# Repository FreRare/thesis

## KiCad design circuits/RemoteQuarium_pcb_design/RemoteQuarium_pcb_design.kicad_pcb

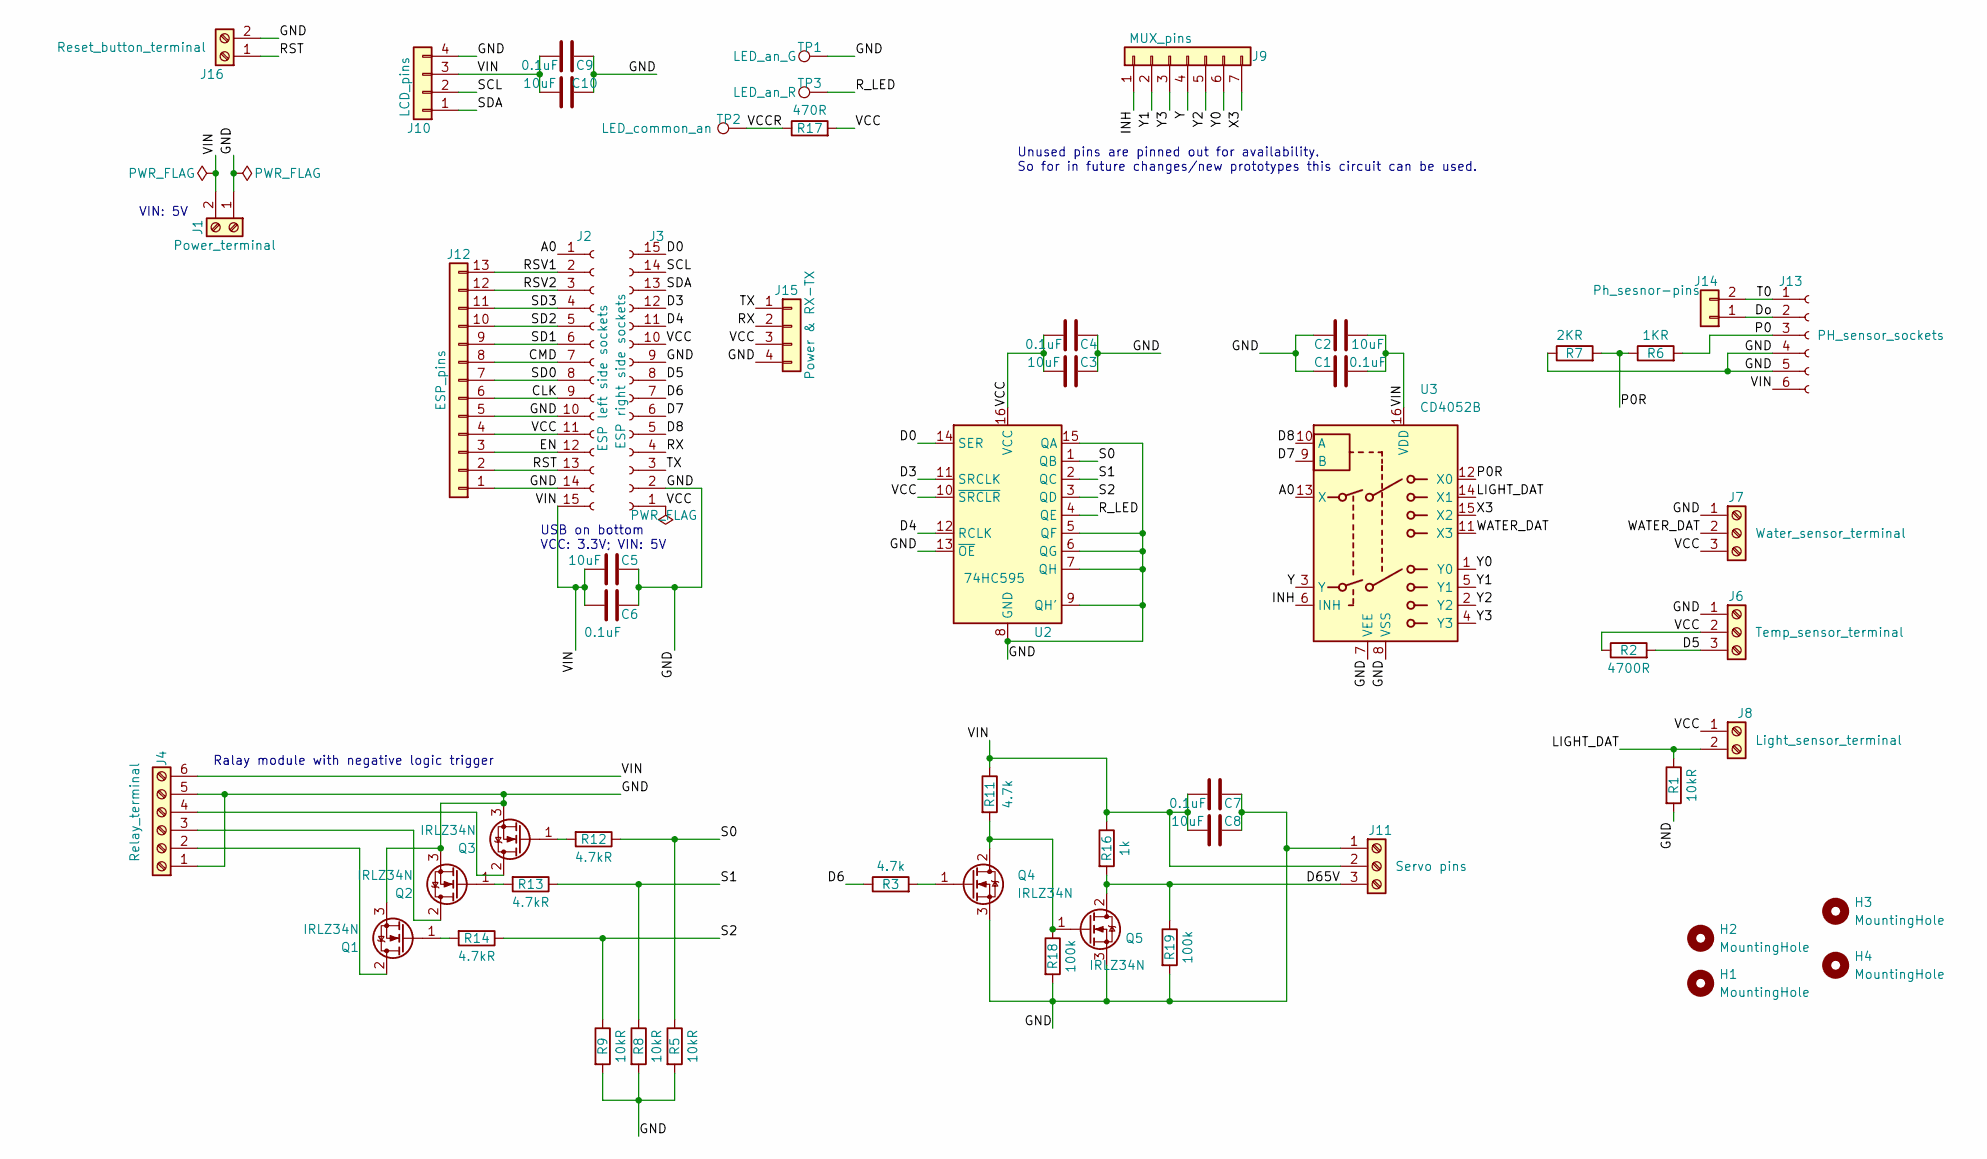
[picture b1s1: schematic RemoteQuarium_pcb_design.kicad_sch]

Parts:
C1, C4, C6, C7, C9: 0.1uF; CP_Radial_D6.3mm_P2.50mm
C2, C3, C5, C8, C10: 10uF; CP_Radial_D6.3mm_P2.50mm
H1, H2, H3, H4: MountingHole; MountingHole_2.5mm
J1: Power_terminal; TerminalBlock_Phoenix_MPT-0,5-2-2.54_1x02_P2.54mm_Horizontal
J2: ESP left side sockets; PinSocket_1x15_P2.54mm_Vertical
J3: ESP right side sockets; PinSocket_1x15_P2.54mm_Vertical
J4: Relay_terminal; TerminalBlock_Phoenix_MPT-0,5-6-2.54_1x06_P2.54mm_Horizontal
J6: Temp_sensor_terminal; TerminalBlock_Phoenix_MPT-0,5-3-2.54_1x03_P2.54mm_Horizontal
J7: Water_sensor_terminal; TerminalBlock_Phoenix_MPT-0,5-3-2.54_1x03_P2.54mm_Horizontal
J8: Light_sensor_terminal; TerminalBlock_Phoenix_MPT-0,5-2-2.54_1x02_P2.54mm_Horizontal
J9: MUX_pins; PinHeader_1x07_P2.54mm_Vertical
J10: LCD_pins; PinHeader_1x04_P2.54mm_Horizontal
J11: Servo pins; TerminalBlock_Phoenix_MPT-0,5-3-2.54_1x03_P2.54mm_Horizontal
J12: ESP_pins; PinHeader_1x13_P2.54mm_Vertical
J13: PH_sensor_sockets; PinSocket_1x06_P2.54mm_Horizontal
J14: Ph_sesnor-pins; PinHeader_1x02_P2.54mm_Vertical
J15: Power & RX-TX; PinHeader_1x04_P2.54mm_Vertical
J16: Reset_button_terminal; TerminalBlock_Phoenix_MPT-0,5-2-2.54_1x02_P2.54mm_Horizontal
Q1, Q2, Q3, Q4, Q5: IRLZ34N; TO-220-3_Vertical
R1, R5, R8, R9: 10kR; R_Axial_DIN0207_L6.3mm_D2.5mm_P7.62mm_Horizontal
R2: 4700R; R_Axial_DIN0207_L6.3mm_D2.5mm_P7.62mm_Horizontal
R3, R11: 4.7k; R_Axial_DIN0207_L6.3mm_D2.5mm_P7.62mm_Horizontal
R6: 1KR; R_Axial_DIN0207_L6.3mm_D2.5mm_P7.62mm_Horizontal
R7: 2KR; R_Axial_DIN0207_L6.3mm_D2.5mm_P7.62mm_Horizontal
R12, R13, R14: 4.7kR; R_Axial_DIN0207_L6.3mm_D2.5mm_P7.62mm_Horizontal
R16: 1k; R_Axial_DIN0207_L6.3mm_D2.5mm_P7.62mm_Horizontal
R17: 470R; R_Axial_DIN0207_L6.3mm_D2.5mm_P7.62mm_Horizontal
R18, R19: 100k; R_Axial_DIN0207_L6.3mm_D2.5mm_P7.62mm_Horizontal
TP1: LED_an_G; TestPoint_2Pads_Pitch2.54mm_Drill0.8mm
TP2: LED_common_an; TestPoint_2Pads_Pitch2.54mm_Drill0.8mm
TP3: LED_an_R; TestPoint_2Pads_Pitch2.54mm_Drill0.8mm
U2: 74HC595; DIP794W45P254L1969H508Q16
U3: CD4052B; DIP794W45P254L1969H508Q16

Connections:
/A0: J2.1, U3.13 (X)
/CLK: J2.9, J12.6
/CMD: J2.7, J12.8
/D0: J3.15, U2.14 (SER)
/D3: J3.12, U2.11 (SRCLK)
/D4: J3.11, U2.12 (RCLK)
/D5: J3.8, J6.3, R2.2
/D6: J3.7, R3.1
/D7: J3.6, U3.9 (B)
/D8: J3.5, U3.10 (A)
/D65V: J11.3, Q5.2 (D), R16.2, R19.1
/Do: J13.2, J14.1
/EN: J2.12, J12.3
/GND: C1.2, C2.2, C3.2, C4.2, C5.2, C6.2, C7.2, C8.2, C9.2, C10.2, J1.1, J2.10, J2.14, J3.2, J3.9, J4.1, J4.5, J6.1, J7.1, J10.4, J11.1, J12.1, J12.5, J13.4, J13.5, J15.4, J16.2, Q1.3 (S), Q2.3 (S), Q3.3 (S), Q4.3 (S), Q5.3 (S), R1.2, R5.2, R7.1, R8.2, R9.2, R18.2, R19.2, TP1.1, U2.5 (QF), U2.6 (QG), U2.7 (QH), U2.8 (GND), U2.9 (QH'), U2.13 (~OE), U2.15 (QA), U3.7 (VEE), U3.8 (VSS)
/INH: J9.1, U3.6 (INH)
/LIGHT_DAT: J8.2, R1.1, U3.14 (X1)
/P0: J13.3, R6.2
/P0R: R6.1, R7.2, U3.12 (X0)
/RST: J2.13, J12.2, J16.1
/RSV1: J2.2, J12.13
/RSV2: J2.3, J12.12
/RX: J3.4, J15.2
/R_LED: TP3.1, U2.4 (QE)
/S0: R5.1, R12.1, U2.1 (QB)
/S1: R8.1, R13.1, U2.2 (QC)
/S2: R9.1, R14.1, U2.3 (QD)
/SCL: J3.14, J10.2
/SD0: J2.8, J12.7
/SD1: J2.6, J12.9
/SD2: J2.5, J12.10
/SD3: J2.4, J12.11
/SDA: J3.13, J10.1
/T0: J13.1, J14.2
/TX: J3.3, J15.1
/VCC: C3.1, C4.1, J2.11, J3.1, J3.10, J6.2, J7.3, J8.1, J12.4, J15.3, R2.1, R17.2, U2.10 (~SRCLR), U2.16 (VCC)
/VCCR: R17.1, TP2.1
/VIN: C1.1, C2.1, C5.1, C6.1, C7.1, C8.1, C9.1, C10.1, J1.2, J2.15, J4.6, J10.3, J11.2, J13.6, R11.1, R16.1, U3.16 (VDD)
/WATER_DAT: J7.2, U3.11 (X3)
/X3: J9.7, U3.15 (X2)
/Y: J9.4, U3.3 (Y)
/Y0: J9.6, U3.1 (Y0)
/Y1: J9.2, U3.5 (Y1)
/Y2: J9.5, U3.2 (Y2)
/Y3: J9.3, U3.4 (Y3)
unnamed: J4.2, Q1.2 (D)
unnamed: J4.3, Q2.2 (D)
unnamed: J4.4, Q3.2 (D)
unnamed: Q1.1 (G), R14.2
unnamed: Q2.1 (G), R13.2
unnamed: Q3.1 (G), R12.2
unnamed: Q4.2 (D), Q5.1 (G), R11.2, R18.1
unnamed: Q4.1 (G), R3.2

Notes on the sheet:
USB on bottom VCC: 3.3V; VIN: 5V
Unused pins are pinned out for availability. So for in future changes/new prototypes this circuit can be used.
Ralay module with negative logic trigger
VIN: 5V

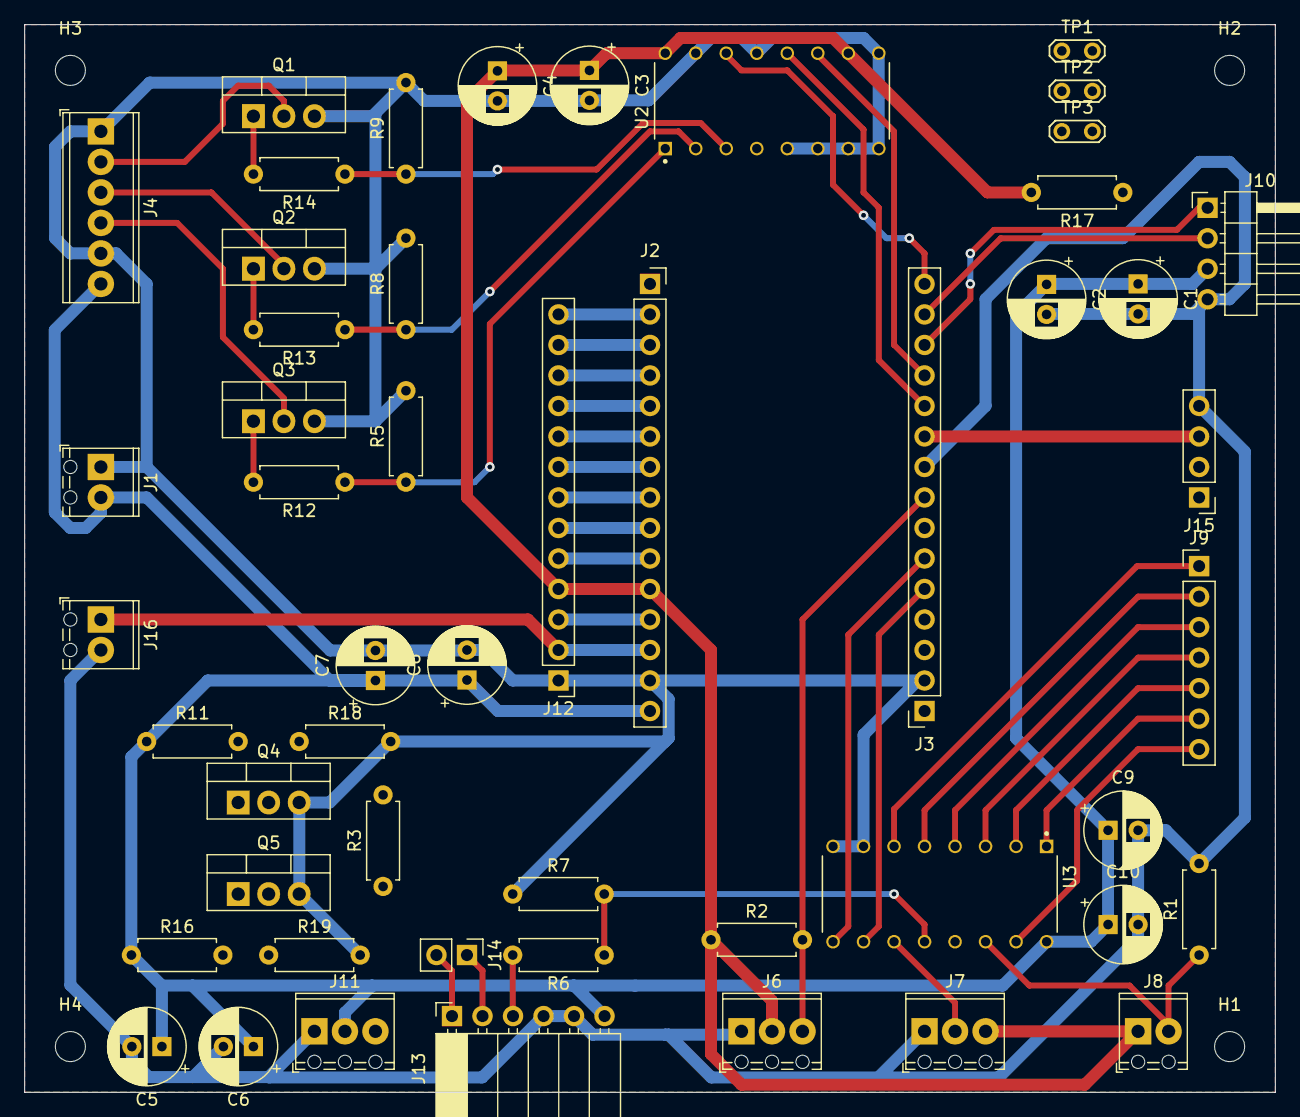
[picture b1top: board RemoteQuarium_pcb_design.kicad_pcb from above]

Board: 4 copper layers, 104.1 x 88.9 mm, 55 parts (0 on the bottom side), 52 nets.

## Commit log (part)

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2023-10-19 ESP programming environment ready in vsc
2023-10-20 Started creting the code for the ESP, all headers are ready except the LCD and actuator handlers
2023-10-20 Updated class diagrams due to simplified memory usage, also created all header and cpp files to be used
2023-10-23 Php api files are ready DB tables created, models are ok, DAO interface implemented and DAO is ready without function implementations. Controls are remaining.
2023-10-23 Deleted unused project directories
2023-10-23 DAO class is ready, needs documentation, but all functions that I can predict will be needed are implemented
2023-10-24 Android app created, activities are ready, and basic navigations are done, still a lot to do...
2023-10-24 API login and registration are ready, should work perfectly, also added DAO documentation
2023-10-25 Created react native project for the phone app
2023-10-26 App is in creation, menubar is ready and login/welcome screen is in progress
2023-10-27 The app is in good progress, login page is ready and login API should work too, registration is upcoming
2023-10-28 Mobile app registration is ready, also API for it, esp programming started, UIHandler is on the way, next is wifi connection.
2023-10-28 WiFi connection is working good on the ESP, also memory handling (EEPROM) is corrected so it wont cause problems anymore. Also UIHandler class is set up for the LCD and working perfectly
2023-10-29 ESP program is handling wifi config and connection, also get's the ID for the system, if not stored before, also the LCD handling is done well. In the phone app the registration and login is working,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
2023-10-29 App home screen is on the way, added data displayer views, also made a better color scheme.
2023-10-30 Simplyfied registration and login in the app, also added user handling to login and registartion, with token based authorization. Made a service for the authorization methods, also auto login should 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
2023-10-31 Phone app updates are in prevoius commit, this is for the php updates. Added login endpoint for token based authorization.
2023-11-01 So this was a long one.. Tested registration and logni, it should work good now with tokens and system ID check too. Also added user session and token storage so auto login is working now, seems good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
2023-11-02 On ESP made the time handling by NTP server connection in ServerConnector. In the app the menu is working with tab naviation and look kinda cool too. Auto login is still working
2023-11-03 Made a top navigation for remaining screens and added some basics to aquariums screen. The service for it is in work. Also made a flowchart from start to home screen.
2023-11-03 Kinda did the sorting methods, some problem with the size sort, but sort by name works, also somehow there's a an extra space at the bottom of the selectlist.. idk
2023-11-03 Added modifications to db structure, fishCount should be kept track of. In the app the aquarium sorting is working, should add to sort by fish count tho.
2023-11-08 In APP removed sorting from aquariums screen added search instead, it works good now. Added layout to configs screen and also a select. Corrected the ER diagram to the actual DB.
2023-11-09 Config screen in app is getting there, added data displayers and edit form, form is not ready tho.
2023-11-09 Added daily time sync to the code
2023-11-09 Added time sync and local RTC timekeeping to the code.
2023-11-09 Added enum types
2023-11-11 Esp code enums are working now, also added clock format.
2023-11-11 Pulled from main
2023-11-11 Removed preferred light from configuration, it seems unnecessary (removed it from api, esp code and react too). We'll just measure the light that's it.
2023-11-11 Not fully ready, but time picker is working, still need to add feeding, but that's a different and unique story.
2023-11-12 Dynamic form is working good so far, needs a lot of styling but works and updates data perfectly. Weird re-rendering things tho in the segmentDisplayer component...
2023-11-14 Made the main ESP code with char* instead of string, may solve the freeze out issues. Also when getting system id from api it saves a default config to the system, can be edited from app anytime. Nee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
2023-11-14 Also removed unnecessary data from esp config, and simplified the configstatus enum.
2023-11-16 Generated some logo options they're in pics
2023-11-16 Config edit form should be working good, still need db connection tho, but the styling is cool. Also made a basic profile screen. Also on the form it can be validated and alert a message with confirm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
2023-11-16 Modified aquarium edit form so now it works as creating form too, still need db connection to all. Corrigated welcomescreen and changed default values of config so when creating an aquarium it can be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
2023-11-20 User edit form added, not tested, password change form not ready. Thesis rewritten to structural preferences.
2023-11-22 Finished all forms in app, only stats page is remaining now on frontend and small edit onedit password from on profile. Still need to do backend and services.
2023-11-23 Removed 2 unnecessary lines from sql tables xd
2023-11-23 Added databse connection to aquariums page in app, almost finished elméleti áttekintés and added API for aquarium managment and config too
2023-11-24 Solved broken LCD problem, alsoadded onfig updating to esp code, should work, never tested. Also resolved some minor things in the esp code.
2023-11-24 Aquarium update is working, need to implement deletion fetch and also the method for esp to remove system id. Need to make config service in app.
2023-11-24 Added deletion.
2023-11-25 Update should work good now, login issue fixed, also added keyboard dismission if clicking anywhere on screen. Edited inputs so now they look good.
2023-11-26 Config edit is foolproof now, I mean form validation is done good. Added full documentation to Config dynamic form, and to layout. A lot of documentation to be done xd.
2023-11-27 MAde a lot of documentation, added aquarium loading to user at the beggining. Should store it in storage between session per user (Can do if after new login delete the previous one)
2023-11-27 Aquariums are loaded along with user in useUser hook. Aquariums screen is updateable with pull down on screen.
2023-11-30 Added stats screen, still need to work on data handling. Config needs to be tested but seems ok so far. Need to work on ESP now.
2023-11-30 App is ready except profile forms and stats screen.
2023-12-04 Added config update on startup and also periodic updates. Created a deviceInit file to manage device initialization things. Also added temp sensor handler code
2023-12-06 ESP confg update is working, ready to do actuators and sensor data porting. PH sensor is reading contant data IDK why..
2023-12-08 Sensor data sending to db is working, need to add actuators and done!
2023-12-09 Added sttaus checking need to do decision making and acting.
2023-12-10 Added actuator handling on esp and error codes enum in php.
2023-12-14 Moved php files to folders, added token update logic (every login or signup creates a new token so last device will be notified, should remove token on logout). Added delete configrmation and logic, 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
2023-12-16 Config handler is working on basics still need to test most of the statuses but should work - also OL on and off times are checked, off cannot be lower than on bc of logic issues. Modified in App too.
2023-12-20 Shift register relay control is working. also added error led and feeder pins to the shift register. Feed funtion and led turn function added too.
2023-12-21 Added chart date range selector in app (simplified the options similar to revolut xd)
2023-12-23 Added new design, also designed stats screen and date ranges are good now. Removed water level alert from everywhere hopefully xd. Edited config edit form to the adjutments.
2023-12-26 Added stats working with real data, auto fill blanks but only day data is working so far still need to add weekly and monthly view data generators. Also fixed config getter in api, need to rewrite db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
2024-01-04 Added a complex algorithm to the stats, it generates viewable data for any number of days. Also for more than 7 days it makes max-min-avg charts.
2024-01-05 Stats screen is working, added dynamic labeling and light and water is displayed as barchart, only for one day! Can add date picker selector later xd.
2024-01-13 Added average to data gathering in the esp code, also found a spot I missed when removing water level alert but now everything should be fixed. And I can add feeder to the HW.
2024-01-19 Tested the ESP and added logging. Sensor sample selection is not working, need a solution!
2024-01-21 Status handler is working good, modified it so it returns an array of statuses, so it can handle multiple status in one minute, but only checks once in every minute. Sensor data posting is working go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
2024-01-26 Added user data update and password change functions. need to be tested but should work.
2024-01-30 Fixed ESP memory leak xd. Fixed wrong samplePeriod enum numbering. Fixed up relay switching. Also added WDT and runtime measuring. Fixed up wrong time formatting in app. Fixed a lot of stuff actually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
2024-01-31 All working as before, added exception logging to server. Relay switching may not work bc 5V supply and 3.3v signal, may need a transistor..
2024-02-01 Added memory logging, there's still an exception 3 somewhere at config update, trying to detremine where... Shift register is still a fucked up thing xd
2024-02-07 Added more complex logging and notification testing should work, app builds and is usable, but need to add react SVG libs for the charts to workgit add .
2024-02-08 App is working finally good, build in dev mode works, fixed profile edit and password change issues. BEFORE THIS COMMIT THE APP WONT RUNgit add . There will be runtime errors due to missing third par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
2024-02-12 Minor changes to the strings and to notification are working, also made a working dev build
2024-02-23 Added template avg function to sensor sampling, need to test it.
2024-02-23 Added esp wifi desription to thesis paper
2024-03-04 Fixed up error logging and added more timeout for wifi connection in case of power outage
2024-03-04 Fixed templete based sensor data median calculations and also added some more dt to sampling, so by calculation sample cycle should be about 45s, extended sw wdt timeout
2024-03-04 Added a fixed 20% data bypass to median calculator for sensor data
2024-03-08 Fixed temp sampling conversion bug (casting to uint from float xd) Also hopefully fixed up too many connections sql error at server.
2024-03-11 Added wificonfig documentation and created base of factory reset
2024-03-16 Modified stats page, so it won't try to load more than 3 times after unsuccessful requests.
2024-03-16 Added factory reset function (with valid while loop xd) also added sampling on boot, so will have displayable data after startup
2024-03-20 Modified DB so user have an ID now. Also fixed (hopefully need to double check) statistics data fill is scaled with sample period. Added factory reset function which is working. All other should work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
2024-03-20 Solved datetime problem on home page.
2024-03-23 Created a basic website for admin purposes.
2024-03-25 Added users and systems page (basic) also modified circuit with decoupling capacitors
2024-03-29 Added a good log view page, also started with user and system pages
2024-03-31 Created a pretty nice layout for website, also made a good database handler page
2024-04-23 Removed cleaning and waterchange from app since it won't be implemented and made the level shifter working
2024-04-24 Fixed config/feeding portion alert user interaction
2024-04-28 Added valid ph measureing and fixed negative logic LED
2024-05-01 Resolved ntp summer time change using timezones
2024-05-01 Gitignore update
2024-05-01 Added exact day to no samples alert msg
2024-05-01 Made smooth loading animation in app welcome screen for user data loading
2024-05-11 Moved sha hashing to client side
2024-05-11 Saved thesis
2024-05-12 Can be reviewd
2024-05-12 Fixed some bugs
2024-05-12 Fixed water sensor reading and some other issues
2024-05-12 Should be ready to go
